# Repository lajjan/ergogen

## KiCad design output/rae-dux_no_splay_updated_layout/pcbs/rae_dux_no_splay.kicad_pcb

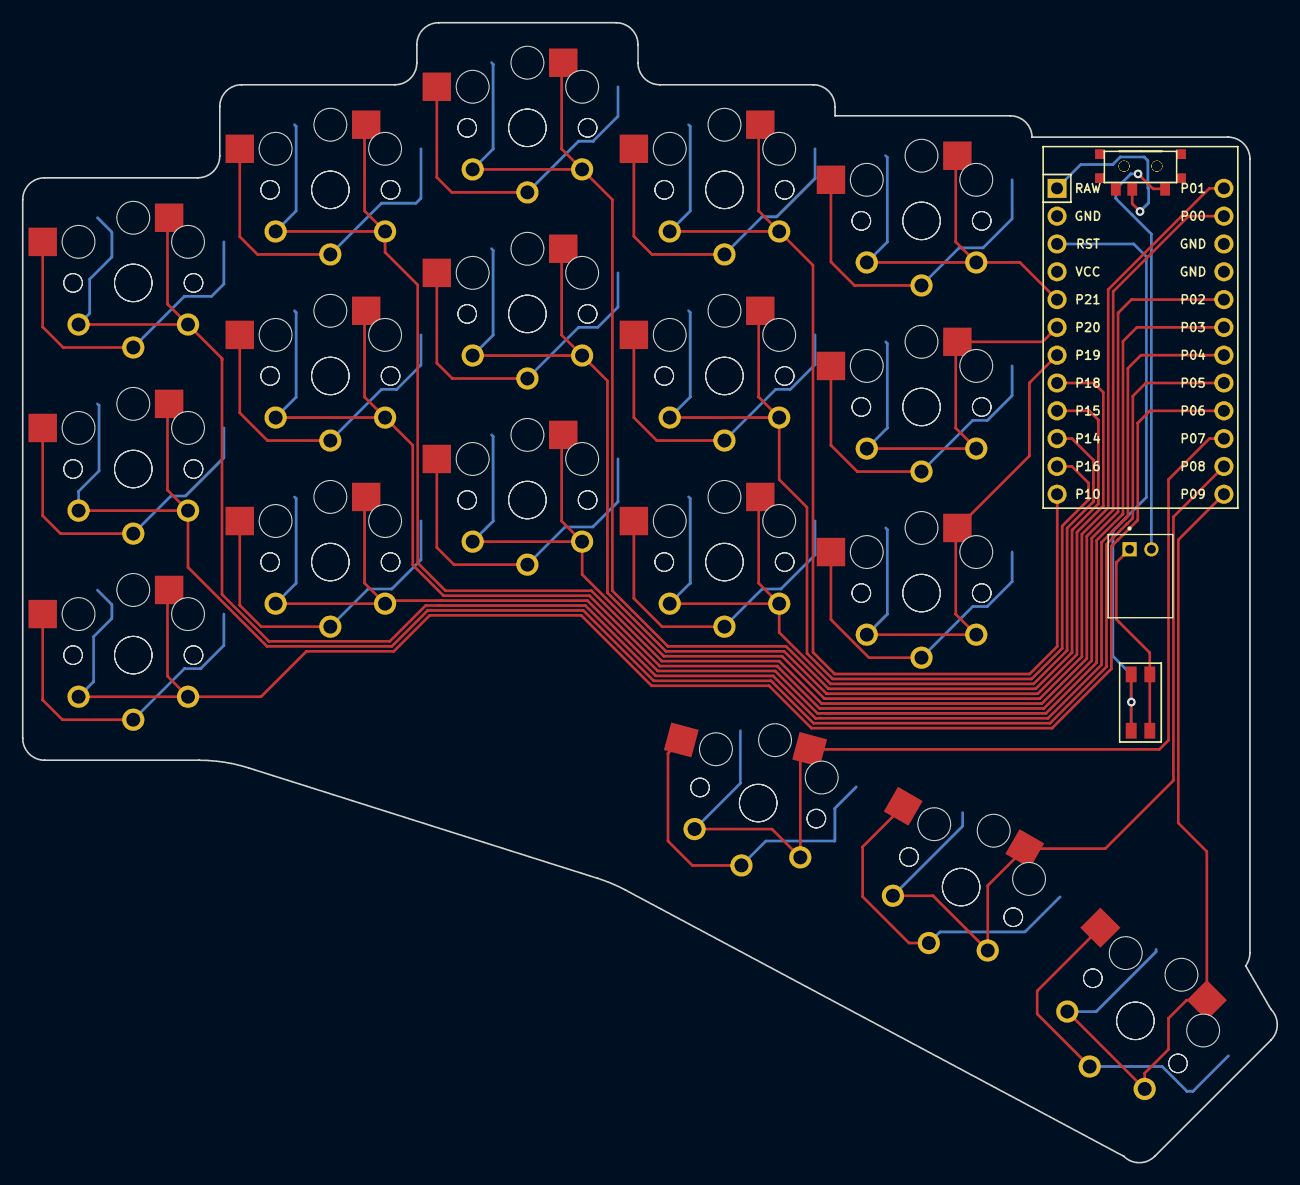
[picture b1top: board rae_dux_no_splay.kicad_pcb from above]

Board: 2 copper layers, 114.6 x 104.1 mm, 41 parts (0 on the bottom side), 22 nets.

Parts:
B1, B2: SW_TACT_EVQ-P2602W
MCU1: ProMicro
S1, S2, S3, S4, S5, S6, S7, S8, S9, S10, S11, S12, S13, S14, S15, S16, S17, S18, S19, S20, S21, S22, S23, S24, S25, S26, S27, S28, S29, S30, S31, S32, S33, S34, S35, S36: PG1350
T1, T2: SPDT_C128955

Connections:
Braw: T1.1, T2.1
GND: B1.2, B2.2, MCU1.2, MCU1.15, MCU1.16, S1.2, S2.2, S3.2, S4.2, S5.2, S6.2, S7.2, S8.2, S9.2, S10.2, S11.2, S12.2, S13.2, S14.2, S15.2, S16.2, S17.2, S18.2, S19.2, S20.2, S21.2, S22.2, S23.2, S24.2, S25.2, S26.2, S27.2, S28.2, S29.2, S30.2, S31.2, S32.2, S33.2, S34.2, S35.2, S36.2
P0: MCU1.14, S11.1, S12.1
P1: MCU1.13, S13.1, S14.1
P2: MCU1.17, S9.1, S10.1
P3: MCU1.18, S7.1, S8.1
P4: MCU1.19, S5.1, S6.1
P5: MCU1.20, S3.1, S4.1
P6: MCU1.21, S1.1, S2.1
P7: MCU1.22, S31.1, S32.1
P8: MCU1.23, S33.1, S34.1
P9: MCU1.24, S35.1, S36.1
P10: MCU1.12, S23.1, S24.1
P14: MCU1.10, S19.1, S20.1
P15: MCU1.9, S17.1, S18.1
P16: MCU1.11, S21.1, S22.1
P18: MCU1.8, S15.1, S16.1
P19: MCU1.7, S25.1, S26.1
P20: MCU1.6, S27.1, S28.1
P21: MCU1.5, S29.1, S30.1
RAW: MCU1.1, T1.2, T2.2
RST: B1.1, B2.1, MCU1.3

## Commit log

2022-05-23 Created first custom board, based on Rae-Dux
2022-09-17 Updated board layout, moved thumb and pinky fingers, changed reset switch
